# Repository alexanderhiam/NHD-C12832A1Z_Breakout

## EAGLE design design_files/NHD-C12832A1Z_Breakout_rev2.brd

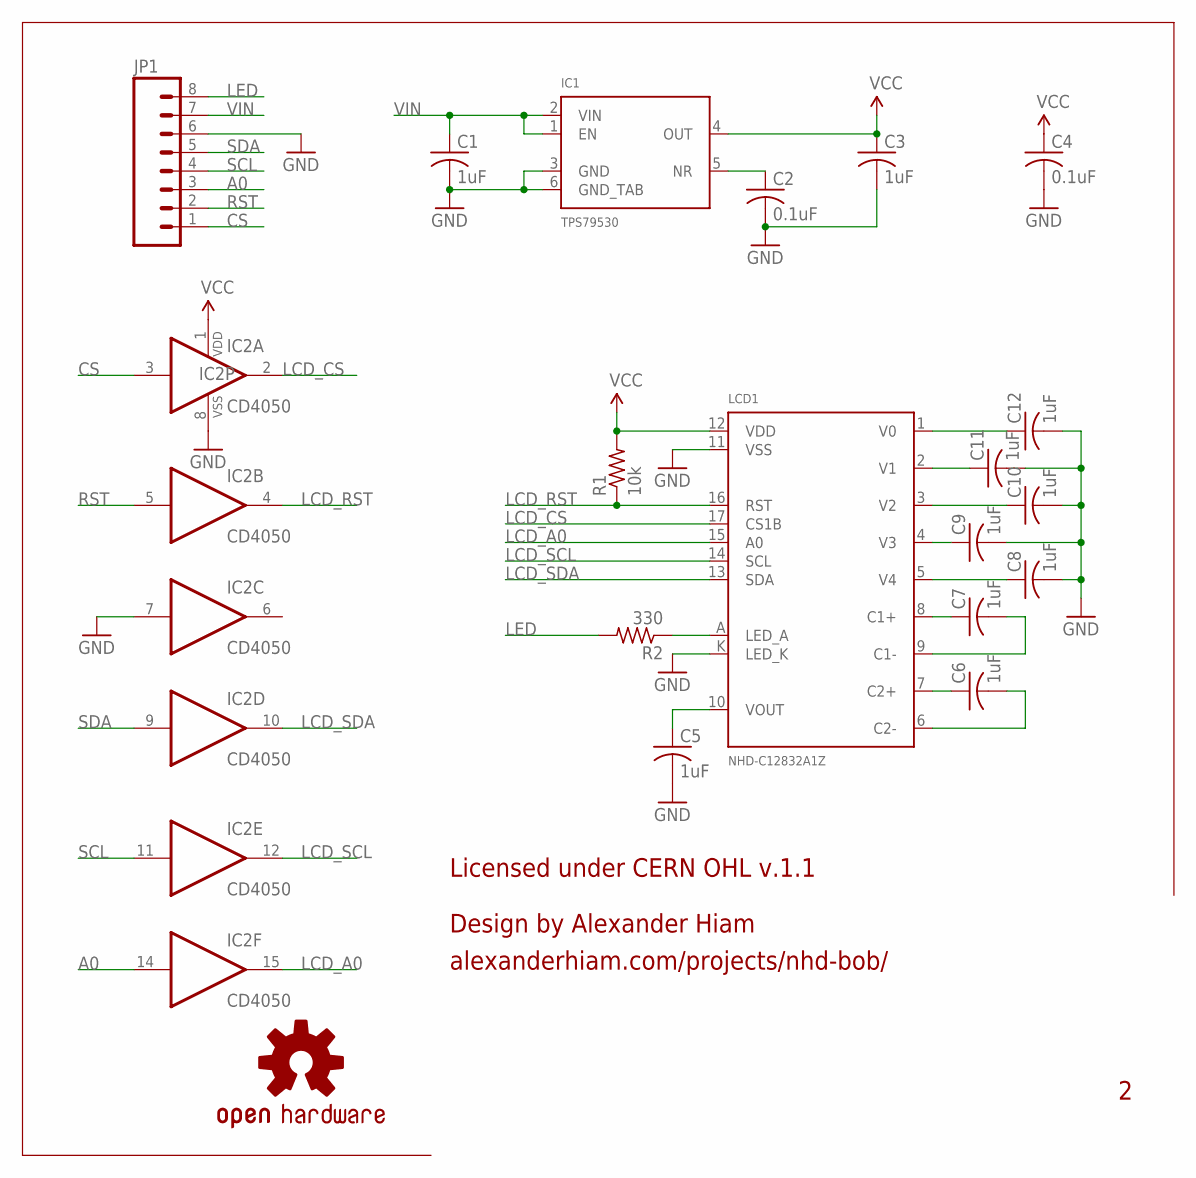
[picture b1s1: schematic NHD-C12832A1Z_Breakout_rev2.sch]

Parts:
C1, C3, C5, C6, C7, C8, C9, C10, C11, C12: 1uF; C0603
C2, C4: 0.1uF; C0603
IC1: TPS79530; SOT223-6
IC2: CD4050; SO16
JP1: M081X08; 1X08
LCD1: NHD-C12832A1Z
R1: 10k; R0603
R2: 330; R0603
U$1: OSHW-LOGOS; OSHW-LOGO-S
U$2: CERN_V1.1_LG

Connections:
A0: IC2.14 (I), JP1.3
CS: IC2.3 (I), JP1.1
GND: C1.2, C2.2, C3.2, C4.2, C5.2, C8.2, C9.2, C10.2, C11.2, C12.2, IC1.3 (GND), IC1.6 (GND_TAB), IC2.7 (I), IC2.8 (VSS), JP1.6, LCD1.11 (VSS), LCD1.K (LED_K)
LCD_A0: IC2.15 (O), LCD1.15 (A0)
LCD_CS: IC2.2 (O), LCD1.17 (CS1B)
LCD_RST: IC2.4 (O), LCD1.16 (RST), R1.1
LCD_SCL: IC2.12 (O), LCD1.14 (SCL)
LCD_SDA: IC2.10 (O), LCD1.13 (SDA)
LED: JP1.8, R2.2
unnamed: C2.1, IC1.5 (NR)
unnamed: LCD1.A (LED_A), R2.1
unnamed: C5.1, LCD1.10 (VOUT)
unnamed: C7.1, LCD1.8 (C1+)
unnamed: C7.2, LCD1.9 (C1-)
unnamed: C6.1, LCD1.7 (C2+)
unnamed: C6.2, LCD1.6 (C2-)
unnamed: C12.1, LCD1.1 (V0)
unnamed: C11.1, LCD1.2 (V1)
unnamed: C10.1, LCD1.3 (V2)
unnamed: C9.1, LCD1.4 (V3)
unnamed: C8.1, LCD1.5 (V4)
RST: IC2.5 (I), JP1.2
SCL: IC2.11 (I), JP1.4
SDA: IC2.9 (I), JP1.5
VCC: C3.1, C4.1, IC1.4 (OUT), IC2.1 (VDD), LCD1.12 (VDD), R1.2
VIN: C1.1, IC1.1 (EN), IC1.2 (VIN), JP1.7

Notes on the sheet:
Design by Alexander Hiam
alexanderhiam.com/projects/nhd-bob/

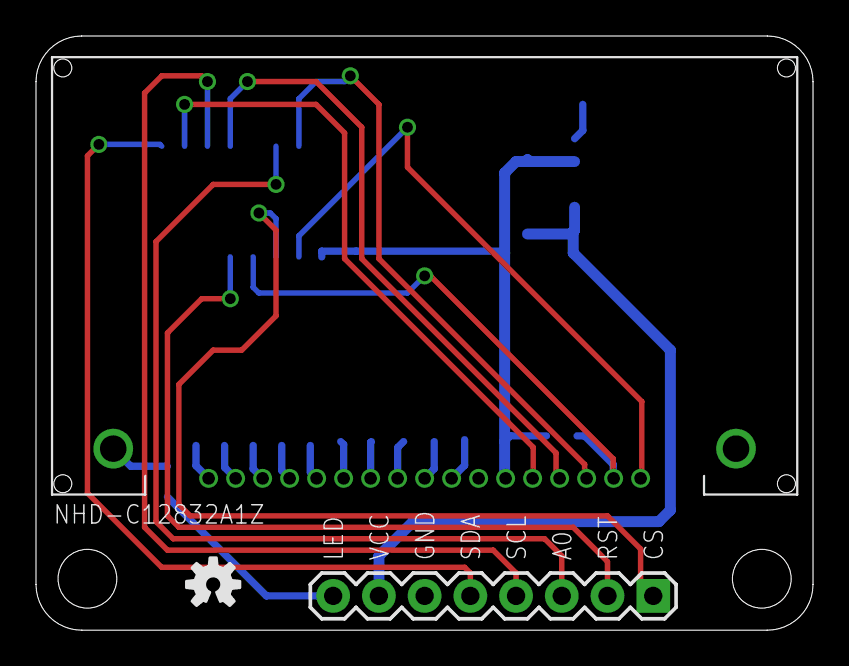
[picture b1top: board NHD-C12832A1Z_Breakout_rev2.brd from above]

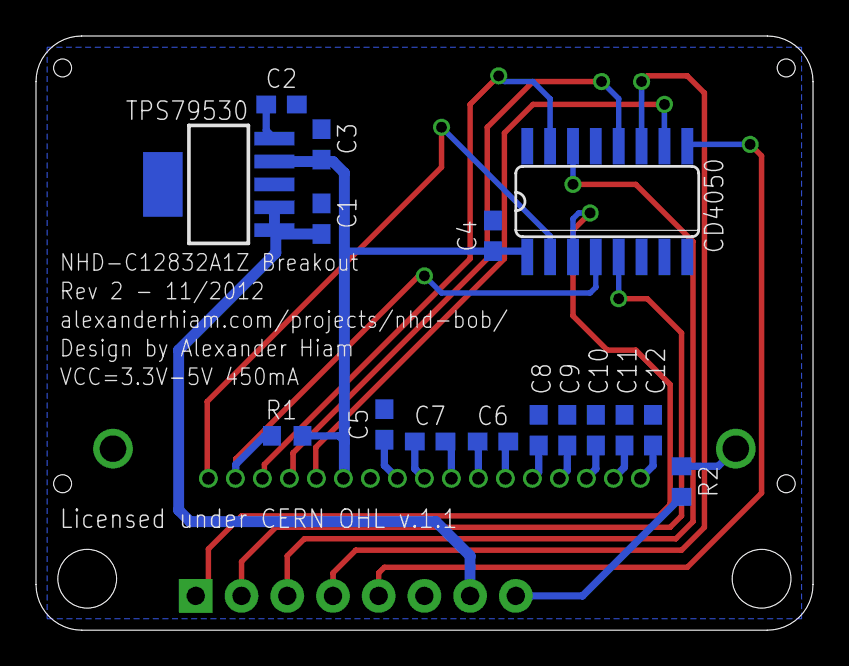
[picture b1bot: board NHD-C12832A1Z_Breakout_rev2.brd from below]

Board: 2 copper layers, 43.2 x 33.0 mm, 20 parts (17 on the bottom side), 26 nets.

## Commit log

2012-12-08 added revision number

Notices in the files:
parts and their libraries:
alexanderhiam: Licensed under CERN OHL v.1.1
SparkFun-Connectors: Licensing: CC v3.0 Share-Alike You are welcome to use this library for commercial purposes.
